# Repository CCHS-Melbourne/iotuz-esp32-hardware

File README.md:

IoTuz - The Internet of Tuz
=============

Welcome to the linux.conf.au 2017 Open Hardware Project.  You can see information about this and other MiniConfs at http://www.openhardwareconf.org/wiki/Main_Page

This year we're bringing a project with the hottest new micro for people to have a play with. The ESP32 is the successor to the hugely popular ESP8266 chip we used for 2016 Open Hardware Project, the (ESPlant, https://github.com/CCHS-Melbourne/ESPlant).

The ESP32 is definitely the big brother of the ESP8266.  Included in it's features: 2.4 GHz Wi-Fi, Bluetooth, Dual Core CPUs

As usual we've got a custom board and some custom software to get you started on your journey!  Check out the subdirectories in this repo for more information.

IoTuz firmware can be found at https://github.com/CCHS-Melbourne/iotuz-esp32-firmware

Hardware assembly instructions
------------------------------
[Workshop assembly instructions](https://github.com/CCHS-Melbourne/IoTuz/wiki/Assembly-Instructions)
for people attending the LCA2017 Open Hardware Mini-Conference.

Software instructions
---------------------

[Software setup instructions](https://github.com/CCHS-Melbourne/IoTuz/wiki/Software-Instructions)

Please see https://github.com/marcmerlin/IoTuz mentioned below for an arduino driver.

Features
--------

[Marc MERLIN has written a driver for the arduino environment](https://github.com/marcmerlin/IoTuz) with support for:
- TFT (hw SPI)
- Touchscreen (hw SPI)
- Replacement touchscreen support (calibration option in case your touchscreen is reversed or has different calibration)
- Rotary Encoder via pin interrupt driven driver
- Support for A and B buttons "hidden" behind the I2C IO multiplexer
- Joystick
- Color LEDs
- Accelerometer
- BME280 (temperature, humidity, pressure)
- IO expander (pcf8574)
- Infrared receiver

For this software, go to: https://github.com/marcmerlin/IoTuz

Getting IoTuz
---------------
You need to clone the IoTuz repo from github, using the `--recursive` option to pick up submodules. If you download a zip file then the submodule parts will be missing, so we recommend using git to get it.

The command is:
```
git clone --recursive https://github.com/CCHS-Melbourne/IoTuz
```

Where to Now?
-------------

Check out (and contribute to) [the wiki](https://github.com/CCHS-Melbourne/IoTuz/wiki). There is a pinout summary, sensor summary, power information, etc.

CREDITS
------------

Made at hackmelbourne.org !

This project was designed by the 2017 linux.conf.au Open Hardware Team!
 - [Bob Powers](https://github.com/rdpowers)
 - [John Spencer](https://github.com/mage0r)
 - [Angus Gratton](https://github.com/projectgus)
 - [Andy Gelme](https://github.com/geekscape)
 - [Jon Oxer](https://github.com/jonoxer)
 - [Mark Wolfe](https://github.com/wolfeidau)
 - [Ian Firns](https://github.com/firnsy)

Art work: Tasmanian Devil ["Tuz" reference](http://www.redbubble.com/people/taniawalker/works/22375875-round-tasmania-vignettes) (C) 2016 by [Tania Walker](http://www.taniawalker.com).  License [CC-BY-NC-SA](https://creativecommons.org/licenses/by-nc-sa/2.0).  This art work is only going to be used on the PCB production run for the [LCA2017 Open Hardware Mini-Conference](http://www.openhardwareconf.org/wiki/OHC2017).

SPECIAL THANKS
------------

[EspressIF](https://espressif.com/) - The company behind the hugely popular ESP8266 chips we used in 2016 and the brand new ESP32 chips we're using this year.  EspressIF has kindly donated the ESP32 chips we'll be using on the boards.

To the [HackMelbourne](http://hackmelbourne.org) community of Melbourne, Australia.

The Desk Solder protectors feature graphics from [Adafruit Reference Cards](https://github.com/adafruit/Reference-Cards).

To all other open-source developers whose countless hours supported every other aspect of this design.

DISTRIBUTION
------------
The specific terms of distribution of this project are governed by the
license referenced below. Please contact the copyright owner if you wish to modify the board for distribution. Please utilize this design for personal or research projects. Please acknowledge all contributors.

LICENSE
-------
Licensed under the TAPR Open Hardware License (www.tapr.org/OHL).
The "LICENSE" file is a copy of this license in plain text format.

Copyright John Spencer, Bob Powers, Angus Gratton, Andy Gelme, Jon Oxer, Mark Wolfe 2016

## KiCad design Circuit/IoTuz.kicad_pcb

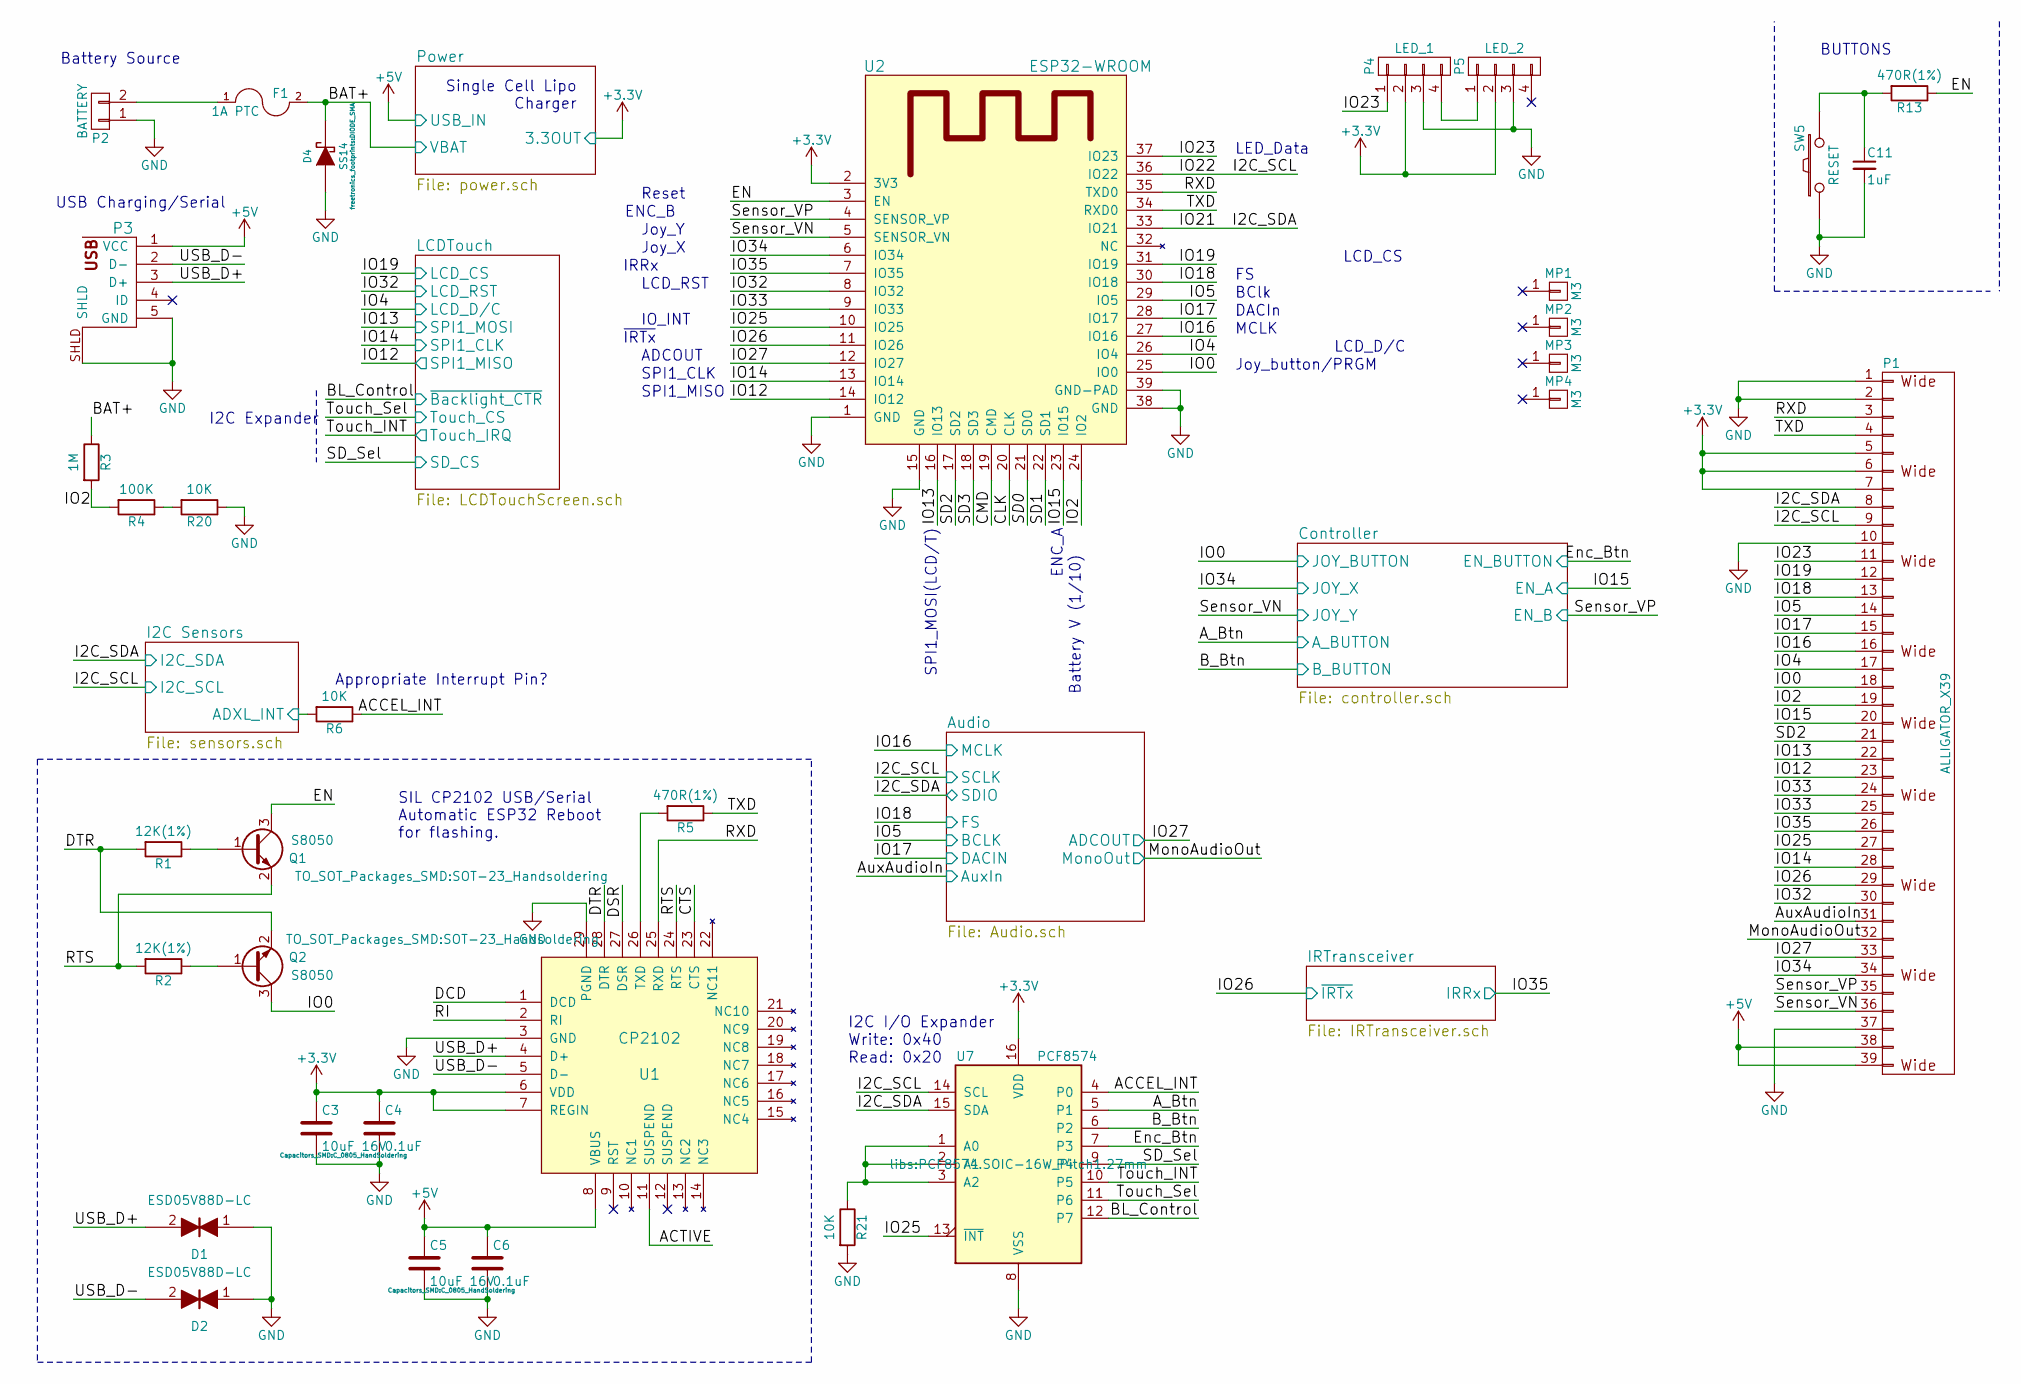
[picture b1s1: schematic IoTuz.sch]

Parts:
C3, C5: 10uF 16V; C_0805_HandSoldering; Manufacturer PN CL21A106KOCLRNC; Digikey PN 1276-2399-1-ND
C4, C6: 0.1uF; C_0603_HandSoldering; Manufacturer PN CC0603KRX7R7BB104; Digikey PN 311-1088-1-ND
C11: 1uF; C_0603_HandSoldering; Manufacturer PN GRM188R61C105KA93D; Digikey PN 490-1536-1-ND
D1, D2: ESD05V88D-LC; SOD-882
D4: SS14; DIODE_SMA; Manufacturer PN SS14; Digikey PN SS14CT-ND
F1: 1A PTC; 1210; Manufacturer PN 0ZCH0050FF2G; Digikey PN 507-1786-1-ND
MP1, MP2, MP3, MP4: M3; MountingHole_3.2mm_M3.IoTuz
P1: ALLIGATOR_X39; alligator_pads.x39.shortened
P2: BATTERY; BH-18650
P3: USB_5PIN_SHELL; USB-MICRO-5pin_PTHMOUNT-Amphenol.10118194-0001LF; Manufacturer PN 10118194-0001LF; Digikey PN 609-4618-1-ND
P4: LED_1; LED_8MM_APA-106
P5: LED_2; LED_8MM_APA-106
Q1, Q2: S8050; SOT-23_Handsoldering; Manufacturer PN MMSS8050-H-TP; Digikey PN MMSS8050-H-TPMSCT-ND
R1, R2: 12K(1%); R_0603_HandSoldering; Manufacturer PN RC0603FR-0712KL; Digikey PN 311-12.0KHRCT-ND
R3: 1M; R_0603_HandSoldering; Manufacturer PN RC0603FR-071ML; Digikey PN 311-1.00MHRCT-ND
R4: 100K; R_0603_HandSoldering; Manufacturer PN RC0603JR-07100KL; Digikey PN 311-100KGRCT-ND
R5, R13: 470R(1%); R_0603_HandSoldering; Manufacturer PN RC0603FR-07470RL; Digikey PN 311-470HRCT-ND
R6, R20, R21: 10K; R_0603_HandSoldering; Manufacturer PN RC0603JR-0710KL; Digikey PN 311-10KGRCT-ND
SW5: RESET; SW_PUSHBUTTON_PTH
U1: CP2102; QFN-28-1EP_5x5mm_Pitch0.5mm; Manufacturer PN CP2102-GMR; Digikey PN 336-1160-1-ND
U2: ESP32-WROOM
U7: PCF8574; PCF8574.SOIC-16W_Pitch1.27mm; Manufacturer PN PCF8574T/3,518; Digikey PN 568-1077-1-ND

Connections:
+3V3: C3.1, C4.1, P1.5, P1.6, P1.7, P4.2, P5.2, U1.6 (VDD), U1.7 (REGIN), U2.2 (3V3), U7.16 (VDD); also elsewhere on the board
+5V: C5.1, C6.1, P1.38, P1.39, P3.1 (VCC), U1.8 (VBUS); also elsewhere on the board
/ACCEL_INT: R6.1, U7.4 (P0)
/ACTIVE: U1.11 (SUSPEND)
/A_Btn: U7.5 (P1); also elsewhere on the board
/AuxAudioIn: P1.31; also elsewhere on the board
/BAT+: D4.K, F1.2, R3.1; also elsewhere on the board
/BL_Control: U7.12 (P7); also elsewhere on the board
/B_Btn: U7.6 (P2); also elsewhere on the board
/CLK: U2.20 (CLK)
/CMD: U2.19 (CMD)
/CTS: U1.23 (CTS)
/DCD: U1.1 (DCD)
/DSR: U1.27 (DSR)
/DTR: Q2.2 (E), R1.2, U1.28 (DTR)
/EN: Q1.3 (C), R13.1, U2.3 (EN)
/Enc_Btn: U7.7 (P3); also elsewhere on the board
/I2C Sensors/ADXL_INT: R6.2; also elsewhere on the board
/I2C_SCL: P1.9, U2.36 (IO22), U7.14 (SCL); also elsewhere on the board
/I2C_SDA: P1.8, U2.33 (IO21), U7.15 (SDA); also elsewhere on the board
/IO0: P1.18, Q2.3 (C), U2.25 (IO0); also elsewhere on the board
/IO2: P1.19, R3.2, R4.2, U2.24 (IO2)
/IO4: P1.17, U2.26 (IO4); also elsewhere on the board
/IO5: P1.14, U2.29 (IO5); also elsewhere on the board
/IO12: P1.23, U2.14 (IO12); also elsewhere on the board
/IO13: P1.22, U2.16 (IO13); also elsewhere on the board
/IO14: P1.28, U2.13 (IO14); also elsewhere on the board
/IO15: P1.20, U2.23 (IO15); also elsewhere on the board
/IO16: P1.16, U2.27 (IO16); also elsewhere on the board
/IO17: P1.15, U2.28 (IO17); also elsewhere on the board
/IO18: P1.13, U2.30 (IO18); also elsewhere on the board
/IO19: P1.12, U2.31 (IO19); also elsewhere on the board
/IO23: P1.11, P4.1, U2.37 (IO23)
/IO25: P1.27, U2.10 (IO25), U7.13 (~INT~)
/IO26: P1.29, U2.11 (IO26); also elsewhere on the board
/IO27: P1.33, U2.12 (IO27); also elsewhere on the board
/IO32: P1.30, U2.8 (IO32); also elsewhere on the board
/IO33: P1.24, P1.25, U2.9 (IO33)
/IO34: P1.34, U2.6 (IO34); also elsewhere on the board
/IO35: P1.26, U2.7 (IO35); also elsewhere on the board
/MonoAudioOut: P1.32; also elsewhere on the board
/RI: U1.2 (RI)
/RTS: Q1.2 (E), R2.2, U1.24 (RTS)
/RXD: P1.3, U1.25 (RXD), U2.35 (TXD0)
/SD0: U2.21 (SDO)
/SD1: U2.22 (SD1)
/SD2: P1.21, U2.17 (SD2)
/SD3: U2.18 (SD3)
/SD_Sel: U7.9 (P4); also elsewhere on the board
/Sensor_VN: P1.36, U2.5 (SENSOR_VN); also elsewhere on the board
/Sensor_VP: P1.35, U2.4 (SENSOR_VP); also elsewhere on the board
/TXD: P1.4, R5.1, U2.34 (RXD0)
/Touch_INT: U7.10 (P5); also elsewhere on the board
/Touch_Sel: U7.11 (P6); also elsewhere on the board
/USB_D+: D1.2, P3.3 (D+), U1.4 (D+)
/USB_D-: D2.2, P3.2 (D-), U1.5 (D-)
unnamed: C11.1, R13.2, SW5.2
unnamed: F1.1, P2.2
unnamed: P4.4, P5.1
unnamed: Q1.1 (B), R1.1
unnamed: Q2.1 (B), R2.1
unnamed: R5.2, U1.26 (TXD)
unnamed: R4.1, R20.2
unnamed: R21.1, U7.1 (A0), U7.2 (A1), U7.3 (A2)

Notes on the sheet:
USB Charging/Serial
Battery Source
Single Cell Lipo Charger
SIL CP2102 USB/Serial Automatic ESP32 Reboot for flashing.
BUTTONS
Joy_button/PRGM
ENC_A
ENC_B
Joy_X
Battery V (1/10)
Reset
MCLK
Appropriate Interrupt Pin?
~IRTx
LED_Data
LCD_CS
LCD_RST
LCD_D/C
SPI1_CLK
SPI1_MISO
I2C I/O Expander Write: 0x40 Read: 0x20
I2C Expander
IO_INT
IRRx
Joy_Y
ADCOUT
DACIn
BClk
SPI1_MOSI(LCD/T)

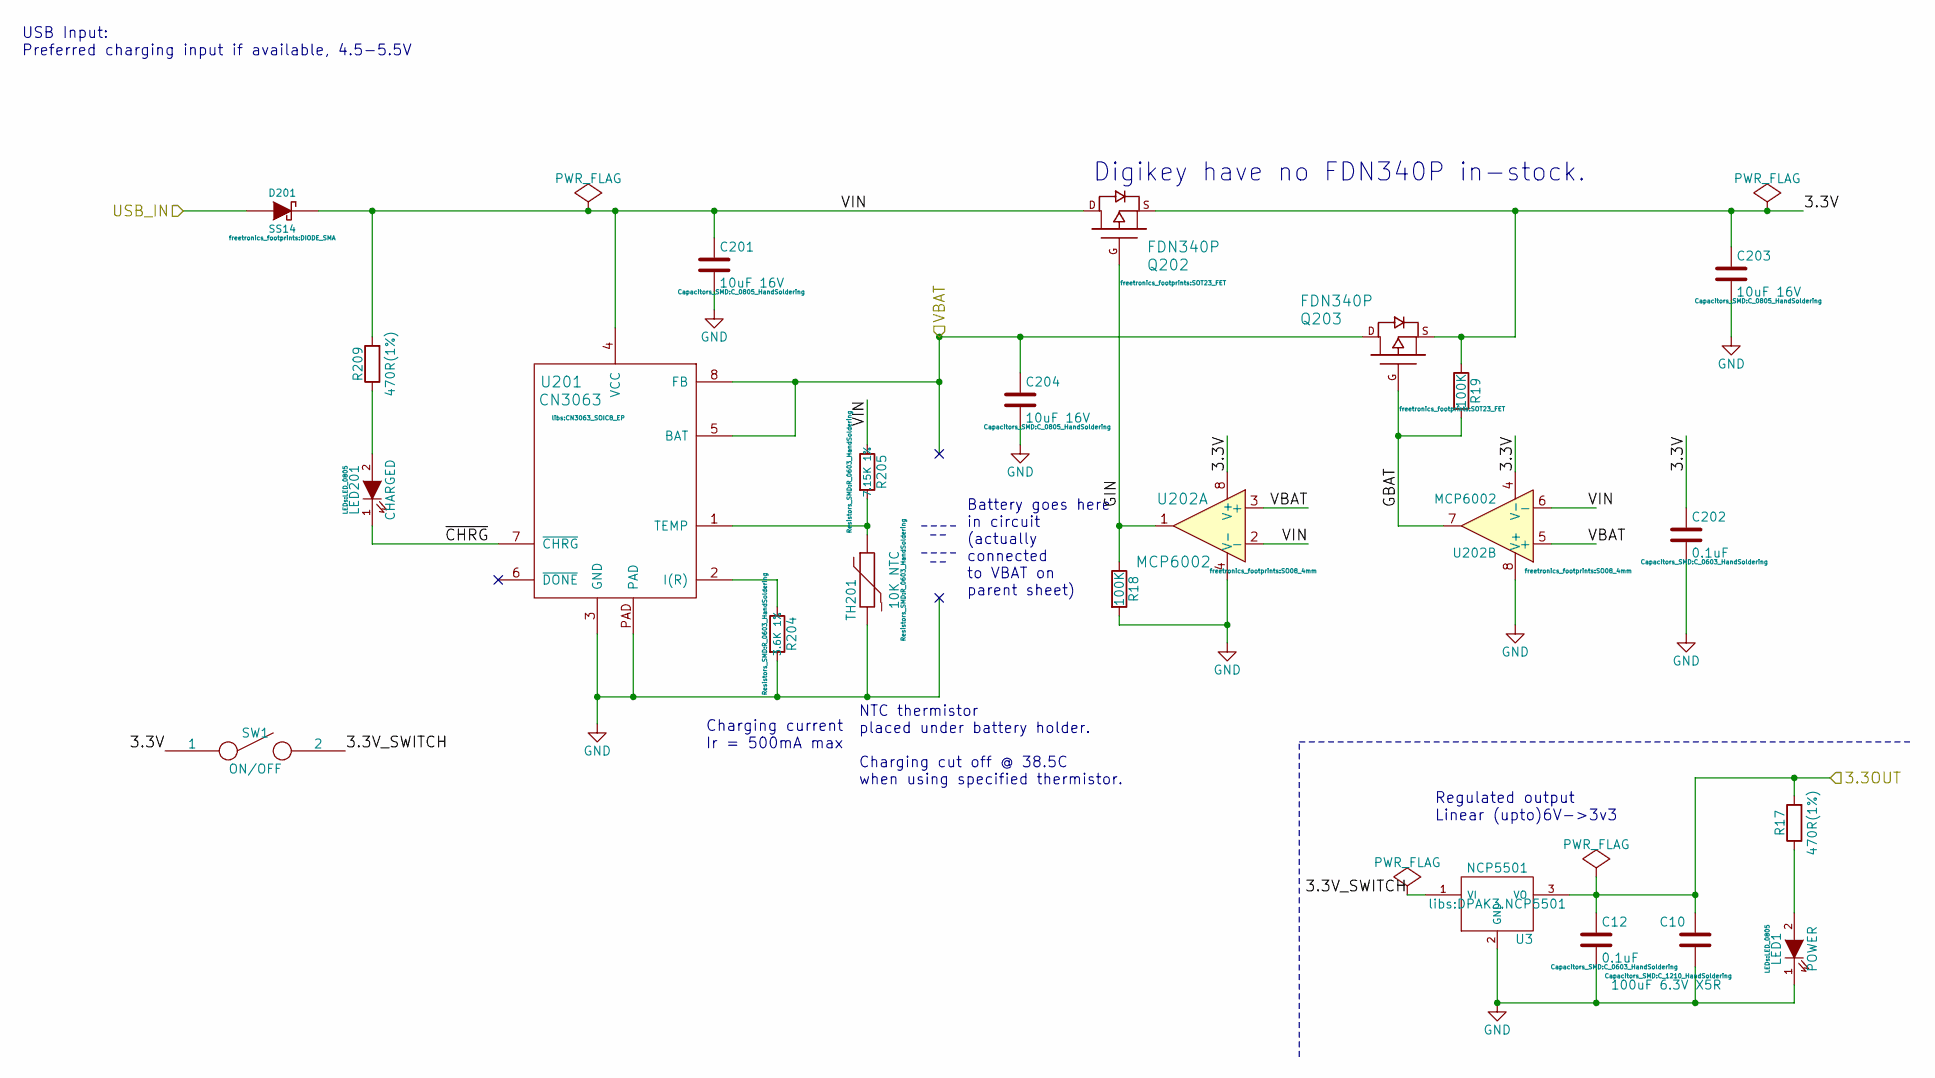
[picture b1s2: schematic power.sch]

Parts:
C10: 100uF 6.3V X5R; C_1210_HandSoldering; Manufacturer PN GRM31CR60J107ME39K; Digikey PN 490-7217-1-ND
C12, C202: 0.1uF; C_0603_HandSoldering; Manufacturer PN CC0603KRX7R7BB104; Digikey PN 311-1088-1-ND
C201, C203, C204: 10uF 16V; C_0805_HandSoldering; Manufacturer PN CL21A106KOCLRNC; Digikey PN 1276-2399-1-ND
D201: SS14; DIODE_SMA; Manufacturer PN SS14; Digikey PN SS14CT-ND
LED1: POWER; LED_0805; Manufacturer PN 150080RS75000; Digikey PN 732-4984-1-ND
LED201: CHARGED; LED_0805; Manufacturer PN LTST-C170KFKT; Digikey PN 160-1413-1-ND
Q202, Q203: FDN340P; SOT23_FET; Manufacturer PN FDN340P; Digikey PN FDN340PCT-ND
R17, R209: 470R(1%); R_0603_HandSoldering; Manufacturer PN RC0603FR-07470RL; Digikey PN 311-470HRCT-ND
R18, R19: 100K; R_0603_HandSoldering; Manufacturer PN RC0603JR-07100KL; Digikey PN 311-100KGRCT-ND
R204: 3.6K 1%; R_0603_HandSoldering; Manufacturer PN RC0603FR-073K6L; Digikey PN 311-3.60KHRCT-ND
R205: 7.15K 1%; R_0603_HandSoldering; Manufacturer PN RC0603FR-077K15L; Digikey PN 311-7.15KHRCT-ND
SW1: ON/OFF; SS12D00
TH201: 10K NTC; R_0603_HandSoldering; Manufacturer PN NCP18XH103F03RB; Digikey PN 490-4800-1-ND
U3: NCP5501; DPAK3.NCP5501; Manufacturer PN NCP5501DT33RKG; Digikey PN NCP5501DT33RKGOSCT-ND
U201: CN3063; CN3063_SOIC8_EP
U202: MCP6002; SO08_4mm; Manufacturer PN MCP6002T-I/SN; Digikey PN MCP6002T-I/SNCT-ND

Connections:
+3V3: C10.2, C12.1, R17.2, U3.3 (VO); also elsewhere on the board
+5V: D201.A; also elsewhere on the board
/BAT+: C204.1, Q203.D, U201.5 (BAT), U201.8 (FB), U202.3 (+), U202.5 (+); also elsewhere on the board
/Power/3.3V_SWITCH: SW1.2, U3.1 (VI)
/Power/GBAT: Q203.G, R19.2, U202.7
/Power/GIN: Q202.G, R18.1, U202.1
/Power/VIN: C201.1, D201.K, Q202.D, R205.1, R209.2, U201.4 (VCC), U202.2 (-), U202.6 (-)
/Power/~CHRG: LED201.1 (K), U201.7 (~CHRG)
unnamed: LED1.2 (A), R17.1
unnamed: LED201.2 (A), R209.1
unnamed: R204.1, U201.2 (I(R))
unnamed: R205.2, TH201.1, U201.1 (TEMP)

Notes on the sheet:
USB Input: Preferred charging input if available, 4.5-5.5V
Charging current Ir = 500mA max
Battery goes here in circuit (actually connected to VBAT on parent sheet)
NTC thermistor placed under battery holder. Charging cut off @ 38.5C when using specified thermistor.
Regulated output Linear (upto)6V->3v3
Digikey have no FDN340P in-stock.

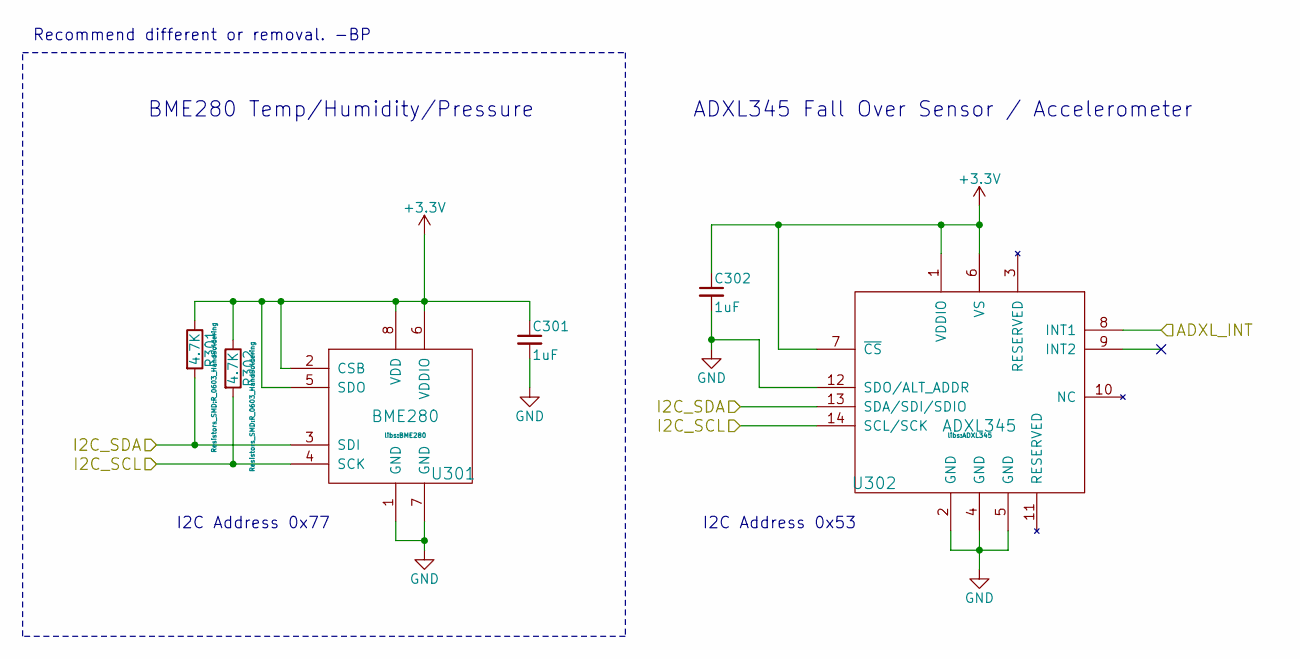
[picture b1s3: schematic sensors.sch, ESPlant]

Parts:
C301, C302: 1uF; C_0603_HandSoldering; Manufacturer PN GRM188R61C105KA93D; Digikey PN 490-1536-1-ND
R301, R302: 4.7K; R_0603_HandSoldering; Manufacturer PN RC0603JR-074K7L; Digikey PN 311-4.7KGRCT-ND
U301: BME280; Manufacturer PN BME280; Digikey PN 828-1063-1-ND
U302: ADXL345; Manufacturer PN ADXL345BCCZ-RL; Digikey PN ADXL345BCCZ-RLCT-ND

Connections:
+3V3: C301.1, C302.1, R301.1, R302.1, U301.2 (CSB), U301.5 (SDO), U301.6 (VDDIO), U301.8 (VDD), U302.1 (VDDIO), U302.6 (VS), U302.7 (~CS); also elsewhere on the board
/I2C Sensors/ADXL_INT: U302.8 (INT1); also elsewhere on the board
/I2C_SCL: R302.2, U301.4 (SCK), U302.14 (SCL/SCK); also elsewhere on the board
/I2C_SDA: R301.2, U301.3 (SDI), U302.13 (SDA/SDI/SDIO); also elsewhere on the board

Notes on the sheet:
I2C Address 0x77
BME280 Temp/Humidity/Pressure
I2C Address 0x53
ADXL345 Fall Over Sensor / Accelerometer
Recommend different or removal. -BP

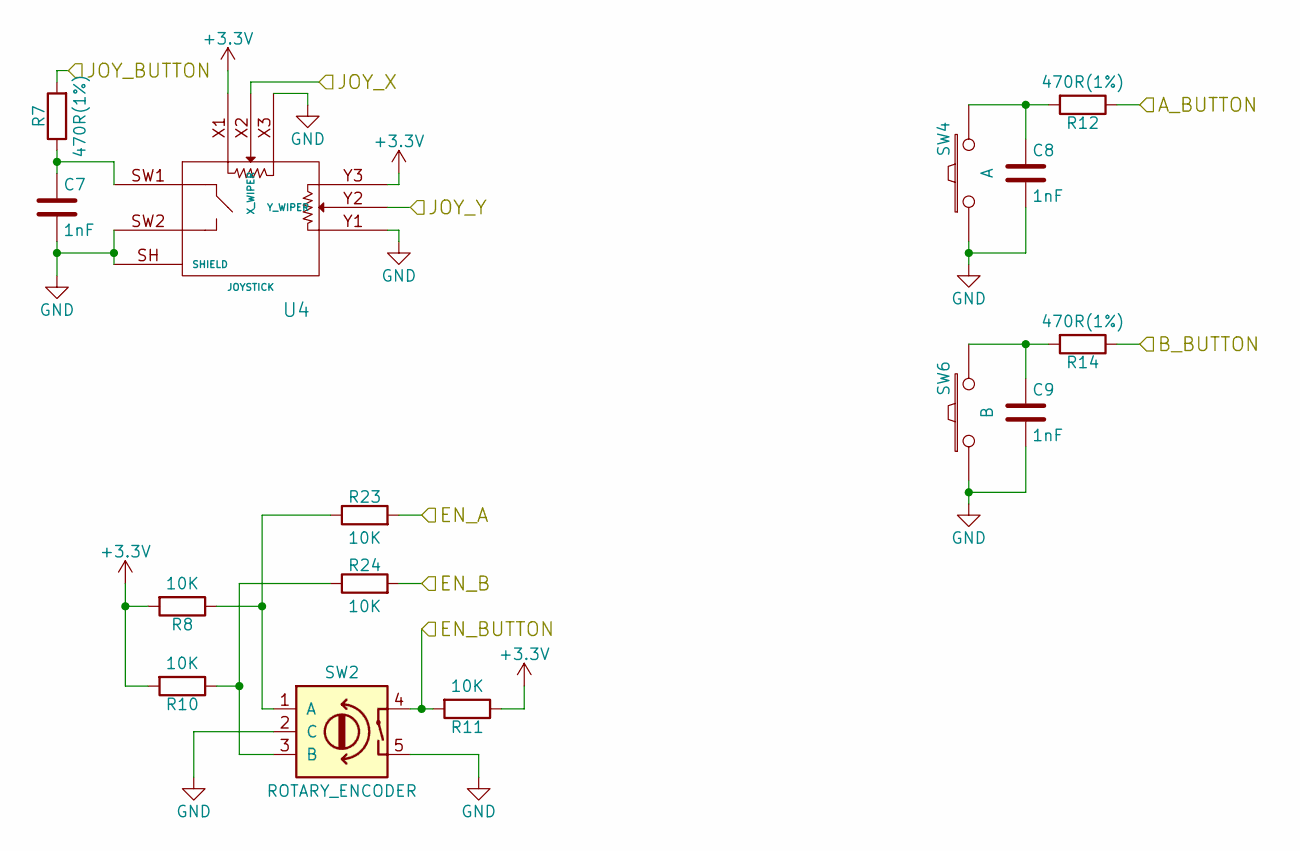
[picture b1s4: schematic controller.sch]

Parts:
C7, C8, C9: 1nF; C_0603_HandSoldering; Manufacturer PN GRM188R71H102KA01D; Digikey PN 490-1494-1-ND
R7, R12, R14: 470R(1%); R_0603_HandSoldering; Manufacturer PN RC0603FR-07470RL; Digikey PN 311-470HRCT-ND
R8, R10, R11, R23, R24: 10K; R_0603_HandSoldering; Manufacturer PN RC0603JR-0710KL; Digikey PN 311-10KGRCT-ND
SW2: ROTARY_ENCODER; EC11
SW4: A; SW_PUSHBUTTON_PTH
SW6: B; SW_PUSHBUTTON_PTH
U4: JOYSTICK; JOYSTICK_W_BUTTON

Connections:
+3V3: R8.2, R10.2, R11.1, U4.X1, U4.Y3; also elsewhere on the board
/A_Btn: R12.1; also elsewhere on the board
/B_Btn: R14.1; also elsewhere on the board
/Enc_Btn: R11.2, SW2.4; also elsewhere on the board
/IO0: R7.2; also elsewhere on the board
/IO15: R23.2; also elsewhere on the board
/IO34: U4.X2 (X_WIPER); also elsewhere on the board
/Sensor_VN: U4.Y2 (Y_WIPER); also elsewhere on the board
/Sensor_VP: R24.2; also elsewhere on the board
unnamed: C7.1, R7.1, U4.SW1
unnamed: C8.1, R12.2, SW4.2
unnamed: C9.1, R14.2, SW6.2
unnamed: R10.1, R24.1, SW2.3 (B)
unnamed: R8.1, R23.1, SW2.1 (A)

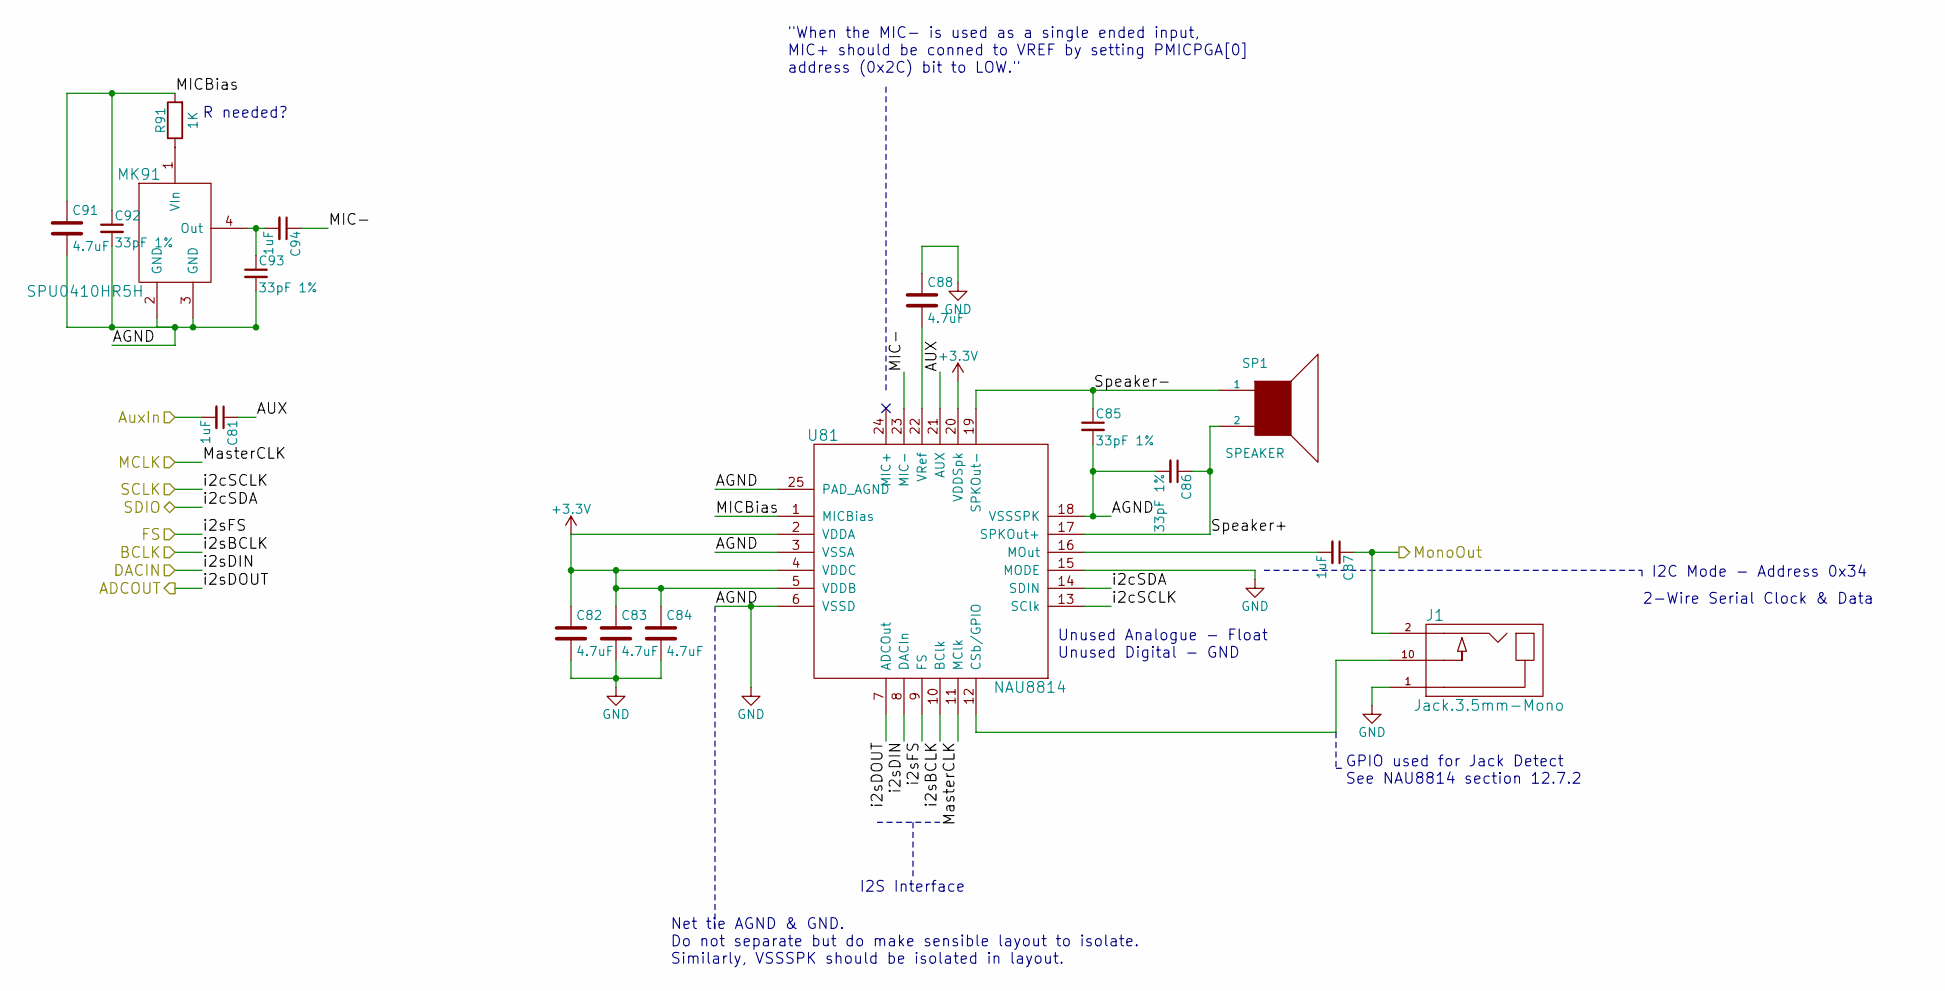
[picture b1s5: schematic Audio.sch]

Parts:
C81, C87, C94: 1uF; C_0603_HandSoldering; Manufacturer PN GRM188R61C105KA93D; Digikey PN 490-1536-1-ND
C82, C83, C84, C88, C91: 4.7uF; C_0603_HandSoldering; Manufacturer PN CL10B475KQ8NQNC; Digikey PN 1276-2087-1-ND
C85, C86, C92, C93: 33pF 1%; C_0603_HandSoldering; Manufacturer PN CL10C330FB8NNNC; Digikey PN 1276-2262-1-ND
J1: Jack.3.5mm-Mono; 3.5mmMonoTSJack.MJ-3523-SMT.Switch; Manufacturer PN MJ-3523-SMT-TR; Digikey PN CP-3523MJCT-ND
MK91: SPU0410HR5H; MEMSMicrophone-SMT-SPU0410HR5H‐PB; Manufacturer PN SPU0410HR5H-PB; Digikey PN 423-1138-1-ND
R91: 1K; R_0603_HandSoldering; Manufacturer PN RC0603JR-071KL; Digikey PN 311-1.0KGRCT-ND
SP1: SPEAKER; CVS-1508.Speaker.PCPins; Manufacturer PN CVS-1508; Digikey PN 102-2498-ND
U81: NAU8814; NAU8814_QFN-24_4x4mm_Pitch0.5mm_EPAD; Manufacturer PN NAU8814YG; Digikey PN NAU8814YG-ND

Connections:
+3V3: C82.1, C83.1, C84.1, U81.2 (VDDA), U81.4 (VDDC), U81.5 (VDDB), U81.20 (VDDSpk); also elsewhere on the board
/Audio/AUX: C81.1, U81.21 (AUX)
/Audio/MIC-: C94.1, U81.23 (MIC-)
/Audio/MICBias: C91.1, C92.1, R91.2, U81.1 (MICBias)
/Audio/Speaker+: C86.1, SP1.2, U81.17 (SPKOut+)
/Audio/Speaker-: C85.1, SP1.1, U81.19 (SPKOut-)
/AuxAudioIn: C81.2; also elsewhere on the board
/I2C_SCL: U81.13 (SClk); also elsewhere on the board
/I2C_SDA: U81.14 (SDIN); also elsewhere on the board
/IO5: U81.10 (BClk); also elsewhere on the board
/IO16: U81.11 (MClk); also elsewhere on the board
/IO17: U81.8 (DACIn); also elsewhere on the board
/IO18: U81.9 (FS); also elsewhere on the board
/IO27: U81.7 (ADCOut); also elsewhere on the board
/MonoAudioOut: C87.1, J1.2; also elsewhere on the board
unnamed: C87.2, U81.16 (MOut)
unnamed: C88.2, U81.22 (VRef)
unnamed: C93.1, C94.2, MK91.4 (Out)
unnamed: J1.10, U81.12 (CSb/GPIO)
unnamed: MK91.1 (VIn), R91.1

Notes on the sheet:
Unused Analogue - Float Unused Digital - GND
"When the MIC- is used as a single ended input, MIC+ should be conned to VREF by setting PMICPGA[0] address (0x2C) bit to LOW."
I2C Mode - Address 0x34
Net tie AGND & GND. Do not separate but do make sensible layout to isolate. Similarly, VSSSPK should be isolated in layout.
2-Wire Serial Clock & Data
I2S Interface
GPIO used for Jack Detect See NAU8814 section 12.7.2
R needed?

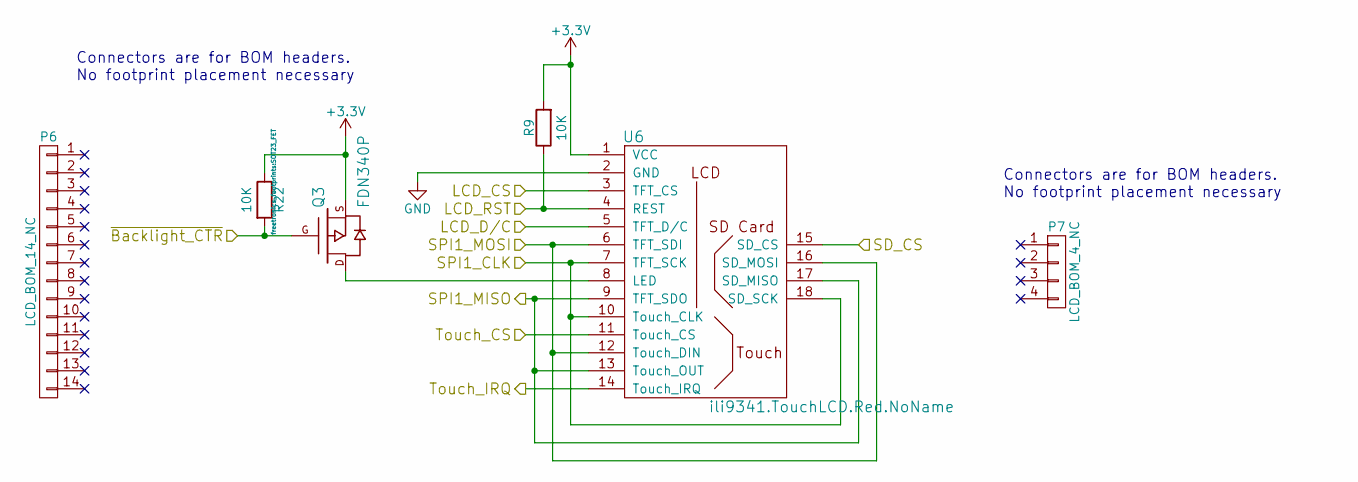
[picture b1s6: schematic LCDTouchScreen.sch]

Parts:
P6: LCD_BOM_14_NC; Manufacturer PN 929974-01-14-RK; Digikey PN 929974E-01-14-ND
P7: LCD_BOM_4_NC; Manufacturer PN 960104-6202-AR; Digikey PN 3M9515-ND
Q3: FDN340P; SOT23_FET; Manufacturer PN FDN340P; Digikey PN FDN340PCT-ND
R9, R22: 10K; R_0603_HandSoldering; Manufacturer PN RC0603JR-0710KL; Digikey PN 311-10KGRCT-ND
U6: ili9341.TouchLCD.Red.NoName; lcdtouchscreen.2.8inch-red.no-name.ili9341-xpt2046

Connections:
+3V3: Q3.S, R9.2, R22.1, U6.1 (VCC); also elsewhere on the board
/BL_Control: Q3.G, R22.2; also elsewhere on the board
/IO4: U6.5 (TFT_D/C); also elsewhere on the board
/IO12: U6.9 (TFT_SDO), U6.13 (Touch_OUT), U6.17 (SD_MISO); also elsewhere on the board
/IO13: U6.6 (TFT_SDI), U6.12 (Touch_DIN), U6.16 (SD_MOSI); also elsewhere on the board
/IO14: U6.7 (TFT_SCK), U6.10 (Touch_CLK), U6.18 (SD_SCK); also elsewhere on the board
/IO19: U6.3 (TFT_CS); also elsewhere on the board
/IO32: R9.1, U6.4 (REST); also elsewhere on the board
/SD_Sel: U6.15 (SD_CS); also elsewhere on the board
/Touch_INT: U6.14 (Touch_IRQ); also elsewhere on the board
/Touch_Sel: U6.11 (Touch_CS); also elsewhere on the board
unnamed: Q3.D, U6.8 (LED)

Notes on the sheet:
Connectors are for BOM headers. No footprint placement necessary

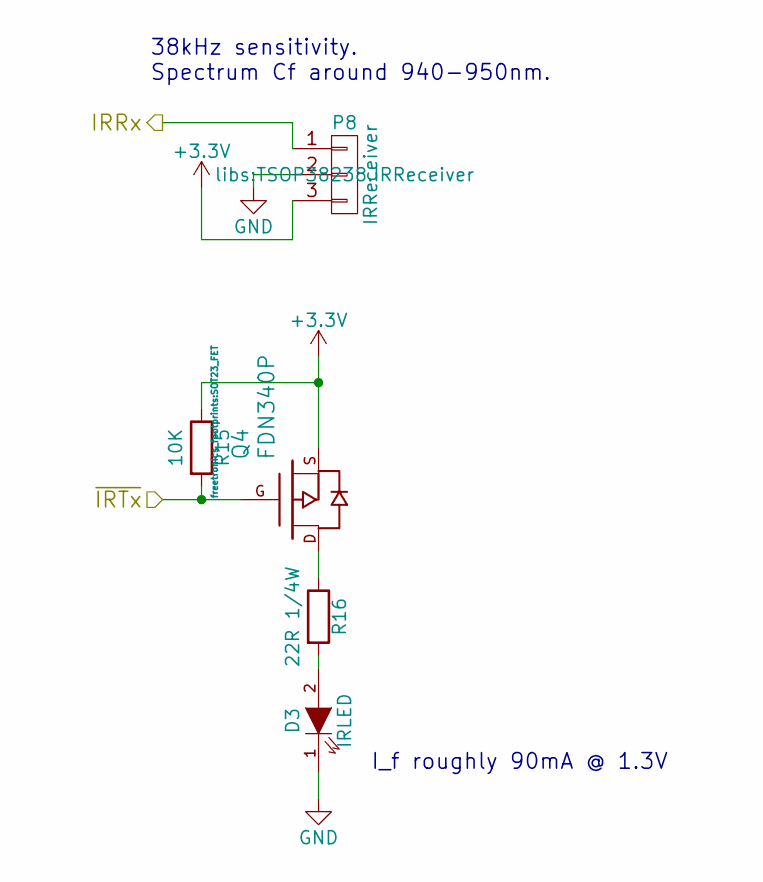
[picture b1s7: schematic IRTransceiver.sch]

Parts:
D3: IRLED; LED-5MM; Manufacturer PN TSAL6200; Digikey PN 751-1204-ND
P8: IRReceiver; TSOP38238.IRReceiver; Manufacturer PN TSOP38238; Digikey PN 751-1227-ND
Q4: FDN340P; SOT23_FET; Manufacturer PN FDN340P; Digikey PN FDN340PCT-ND
R15: 10K; R_0603_HandSoldering; Manufacturer PN RC0603JR-0710KL; Digikey PN 311-10KGRCT-ND
R16: 22R 1/4W; R_0603_HandSoldering; Manufacturer PN ERJ-PA3J220V; Digikey PN P22.00BZCT-ND

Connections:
+3V3: P8.3, Q4.S, R15.1; also elsewhere on the board
/IO26: Q4.G, R15.2; also elsewhere on the board
/IO35: P8.1; also elsewhere on the board
unnamed: D3.2 (A), R16.2
unnamed: Q4.D, R16.1

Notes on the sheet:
38kHz sensitivity. Spectrum Cf around 940-950nm.
I_f roughly 90mA @ 1.3V

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
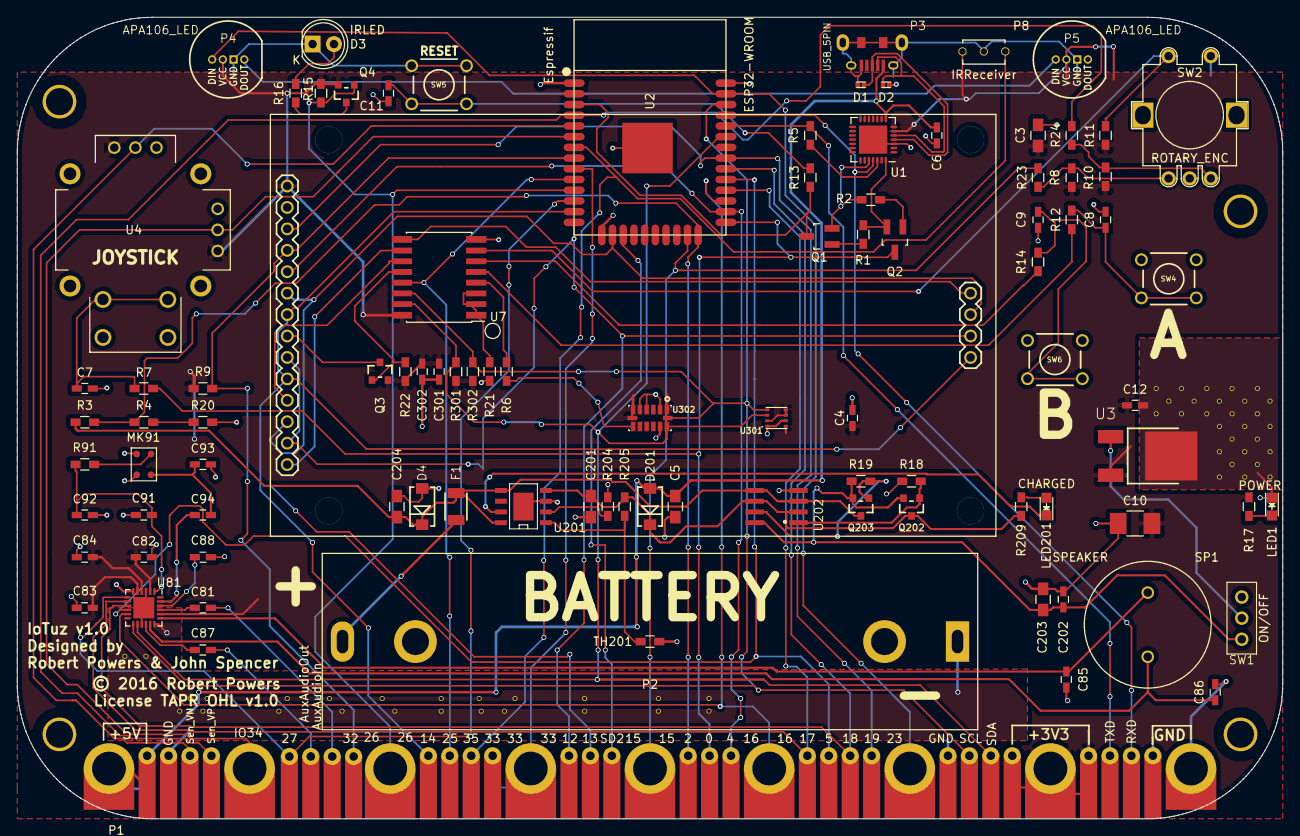
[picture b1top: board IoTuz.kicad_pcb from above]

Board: 2 copper layers, 150.0 x 95.0 mm, 101 parts (0 on the bottom side), 82 nets.

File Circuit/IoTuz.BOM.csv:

Id,Designator,Package,Quantity,Digikey PN,Designation
2,"C4,C6,C202,C12",C_0603_HandSoldering,4,311-1088-1-ND,0.1uF
3,"C7,C8,C9",C_0603_HandSoldering,3,490-3184-1-ND,1nF
4,"C11,C301,C302,C81,C87,C94",C_0603_HandSoldering,6,490-1536-1-ND,1uF
5,"D4,D201",DIODE_SMA,2,SS14CT-ND,SS14
6,F1,1210,1,507-1786-1-ND,1A PTC
7,"Q202,Q203,Q4,Q3",SOT23_FET,4,FDN340PCT-ND,FDN340P
8,"R1,R2",R_0603_HandSoldering,2,311-12.0KHRCT-ND,12K(1%)
9,R3,R_0603_HandSoldering,1,311-1.00MHRCT-ND,1M
10,"R4,R18,R19",R_0603_HandSoldering,3,311-100KGRCT-ND,100K
11,"R5,R7,R12,R13,R14,R17,R209",R_0603_HandSoldering,7,311-470HRCT-ND,470R(1%)
12,"R6,R8,R10,R11,R9,R20,R21,R15,R22",R_0603_HandSoldering,9,311-10KGRCT-ND,10K
13,R204,R_0603_HandSoldering,1,311-3.60KHRCT-ND,3.6K 1%
14,R205,R_0603_HandSoldering,1,311-7.15KHRCT-ND,7.15K 1%
16,U1,QFN-28-1EP_5x5mm_Pitch0.5mm,1,336-1160-1-ND,CP2102
19,U202,SO08_4mm,1,MCP6002T-I/SNCT-ND,MCP6002
23,LED201,LED_0805,1,160-1413-1-ND,LED_ORANGE
24,"Q1,Q2",SOT-23_Handsoldering,2,MMSS8050-H-TPMSCT-ND,S8050
26,"R301,R302",R_0603_HandSoldering,2,311-4.7KGRCT-ND,4.7K
29,U301,BME280,1,828-1063-1-ND,BME280
30,U302,ADXL345,1,ADXL345BCCZ-RLCT-ND,ADXL345
32,TH201,R_0603_HandSoldering,1,490-4800-1-ND,10K NTC
35,D3,LED-5MM,1,751-1204-ND,IRLED
36,R16,R_0603_HandSoldering,1,311-22GRCT-ND,22R
37,SP1,CVS-1508.Speaker.PCPins,1,102-2498-ND,SPEAKER
38,LED1,LED_0805,1,732-4984-1-ND,LED_RED
39,C10,C_1210_HandSoldering,1,490-7217-1-ND,100uF 6.3V X5R
40,P3,USB-MICRO-5pin_PTHMOUNT-Amphenol.10118194-0001LF,1,609-4618-1-ND,USB_5PIN_SHELL
42,U3,DPAK3.NCP5501,1,NCP5501DT33RKGOSCT-ND,NCP5501
43,U7,PCF8574.SOIC-16W_Pitch1.27mm,1,568-1077-1-ND,PCF8574
44,"C82,C83,C84,C88,C91",C_0603_HandSoldering,5,1276-2087-1-ND,4.7uF
45,"C85,C86,C92,C93",C_0603_HandSoldering,4,1276-2262-1-ND,33pF 1%
46,MK91,MEMSMicrophone-SMT-SPU0410HR5H‐PB,1,423-1138-1-ND,SPU0410HR5H
47,R91,R_0603_HandSoldering,1,311-1.0KGRCT-ND,1K
48,"C3,C5,C201,C203,C204",C_0805_HandSoldering,5,1276-2399-1-ND,10uF 16V
49,U81,NAU8814_QFN-24_4x4mm_Pitch0.5mm_EPAD,1,NAU8814YG-ND,NAU8814
52,P8,TSOP38238.IRReceiver,1,751-1227-ND,IRReceiver

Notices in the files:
Circuit/IoTuz.kicad_pcb:
© 2016 Robert Powers
Circuit/sensors.sch:
Copyright (C) 2015 John Spencer & Angus Gratton
